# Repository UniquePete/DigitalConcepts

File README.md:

# DigitalConcepts
Digital Concepts LoRa Project<br />
For project details, see http://digitalconcepts.net.au/iot/<br />
<br />
At the moment, I've just dumped a lot of the project files here. I'll get things better
organised and documented in due course.

## Arduino
Most of the material here comprises the sketches and libraries used in the projects described
on the project website identified above. More details to follow.

The one, essentially stand-alone [JavaScript] application/script here is the syntax highlighter.
This script is based on that developed by Indrek Luuk (see https://circuitjournal.com/syntax-highlighter).
The present version is an in-line version that includes some additional Arduino IDE syntax highlighting,
basic HTML syntax highlighting and optional line numbering. It requires the additional definition of
appropriate CSS style definitions (see Highlight.css).

The script and CSS files need to be placed in appropriate directories and referenced in the Head section
of the relevant HTML file:
```
<head>
	<script type="text/javascript" src="scripts/SyntaxHighlighter.js"></script>
	<script>
		// Run any required Syntax Highlighters when the page loads
		document.addEventListener('DOMContentLoaded', processAllArduinoCode);
		document.addEventListener('DOMContentLoaded', processAllHtmlCode);
	</script>
	<link rel="stylesheet" href="styles/Highlight.css">
</head>
```
For the time being, refer to the SyntaxHighlighter page
(https://digitalconcepts.net.au/arduino/index.php?op=SyntaxHighlighter) on the project website for full
details of the capabilities and how to use the script.

## Eagle
These are the Eagle board and schematic files for the PCBs described on the propject website referenced above.
More details to follow.
 
## Fritzing Parts
These are the Fritzing part files, and the related breadboard images to assist in identification, that are
described on the project website referenced above.
More details to follow.

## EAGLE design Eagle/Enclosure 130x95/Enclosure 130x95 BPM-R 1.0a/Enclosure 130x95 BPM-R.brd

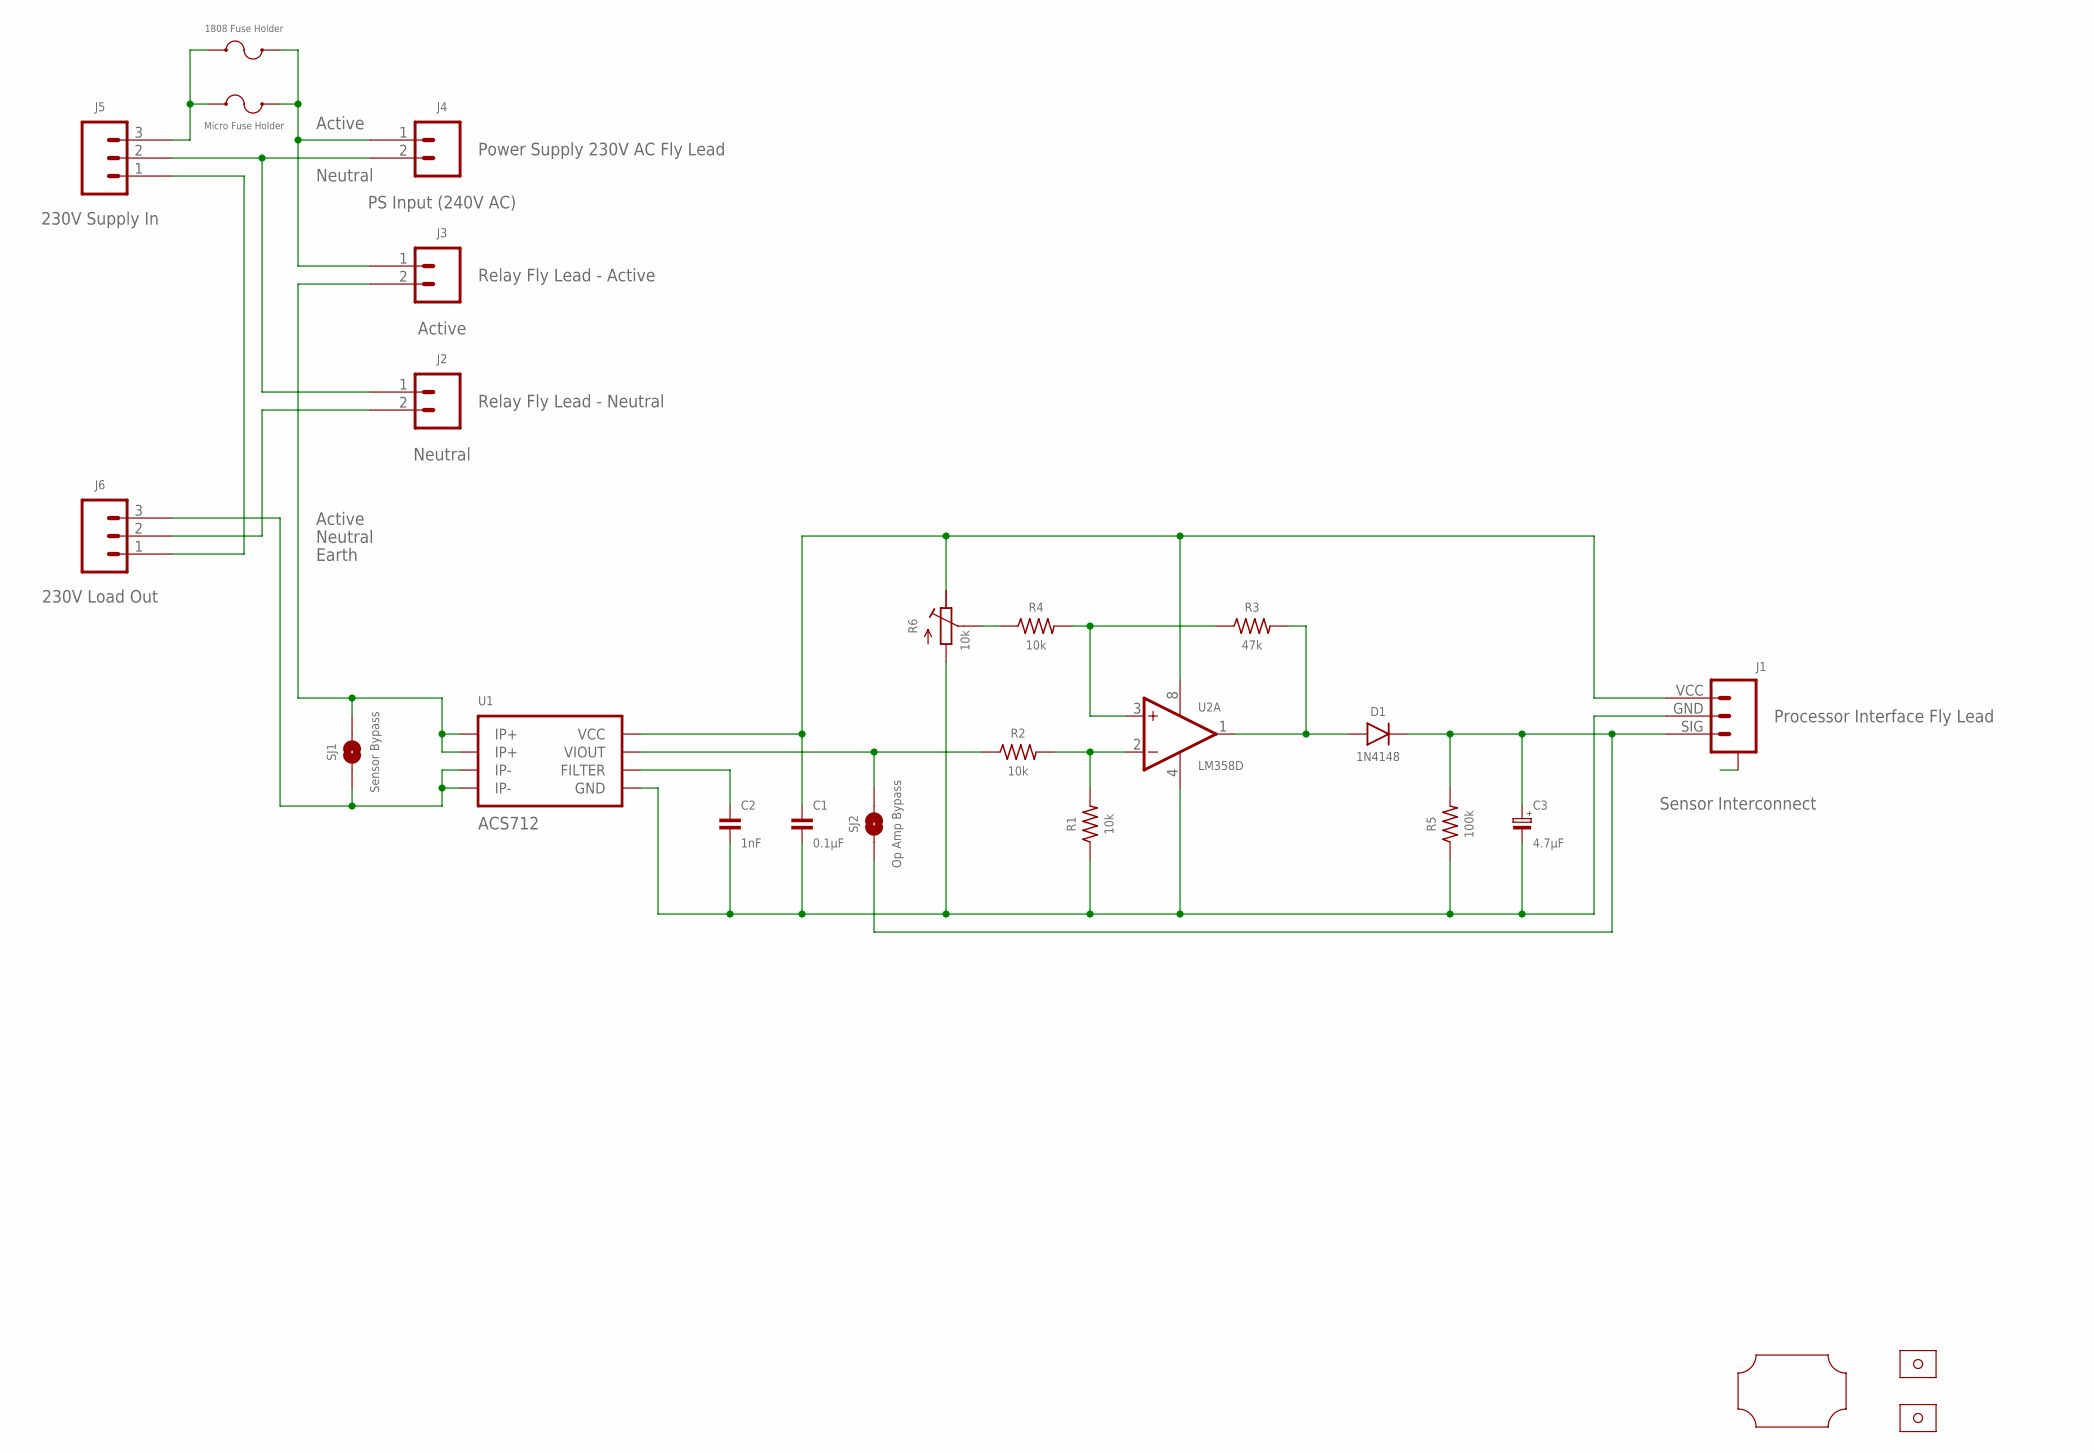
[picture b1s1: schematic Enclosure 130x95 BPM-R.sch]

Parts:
C1: 0.1µF; C0805
C2: 1nF; C0805
C3: 4.7µF; C1206-POLARISED
D1: 1N4148; SOD-323
F2: 1808 Fuse Holder; FUSE-HOLDER-1808
J1: Sensor Interconnect; JST-SH1.0-3-HORIZONTAL-SIG
J2: Neutral; TERMINAL-SCREW-2P
J3: Active; TERMINAL-SCREW-2P
J4: PS Input (240V AC); JST-XH2.4-2-HORIZONTAL
J5: 230V Supply In; TERMINAL-SCREW-3P
J6: 230V Load Out; TERMINAL-SCREW-3P
R1, R2, R4: 10k; R0805
R3: 47k; R0805
R5: 100k; R0805
R6: 10k; RTRIM3386P
SJ1: Sensor Bypass; SJ
SJ2: Op Amp Bypass; SJ
U1: ACS712; SOP-8
U2: LM358D; SOP-8
U$1: PCB-OUTLINE-130X95-MAX-RC-H3; PROTO-130X95-OUTLINE-MAX-RC-H3
U$2: Micro Fuse Holder; FUSE-HOLDER-MICRO
U$4, U$5: STRAIN-RELIEF-SADDLE

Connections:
A: J1.A@1 (A), J1.A@3 (A)
ACTIVE_IN: F2.P$2 (2), J3.1, J4.1, U$2.P$3 (2), U$2.P$4 (2)
ACTIVE_OUT: J3.2, SJ1.2, U1.1 (IP+), U1.2 (IP+)
EARTH: J5.1, J6.1
unnamed: C1.1, J1.VCC (3), R6.1 (E), U1.8 (VCC), U2.8 (V+)
unnamed: C3.1 (+), D1.C (1), J1.SIG (1), R5.2, SJ2.1
unnamed: D1.A (2), R3.2, U2.1 (OUT)
unnamed: R3.1, R4.2, U2.3 (+IN)
unnamed: R4.1, R6.2 (S)
unnamed: F2.P$1 (1), J5.3, U$2.P$1 (1), U$2.P$2 (1)
unnamed: R1.2, R2.2, U2.2 (-IN)
unnamed: J6.3, SJ1.1, U1.3 (IP-), U1.4 (IP-)
unnamed: C1.2, C2.2, C3.2 (-), J1.GND (2), R1.1, R5.1, R6.3 (A), U1.5 (GND), U2.4 (V-)
unnamed: R2.1, SJ2.2, U1.7 (VIOUT)
unnamed: C2.1, U1.6 (FILTER)
NEUTRAL_IN: J2.1, J4.2, J5.2
NEUTRAL_OUT: J2.2, J6.2

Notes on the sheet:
Power Supply 230V AC Fly Lead
Active
Neutral
Relay Fly Lead - Active
Earth
Processor Interface Fly Lead
Relay Fly Lead - Neutral

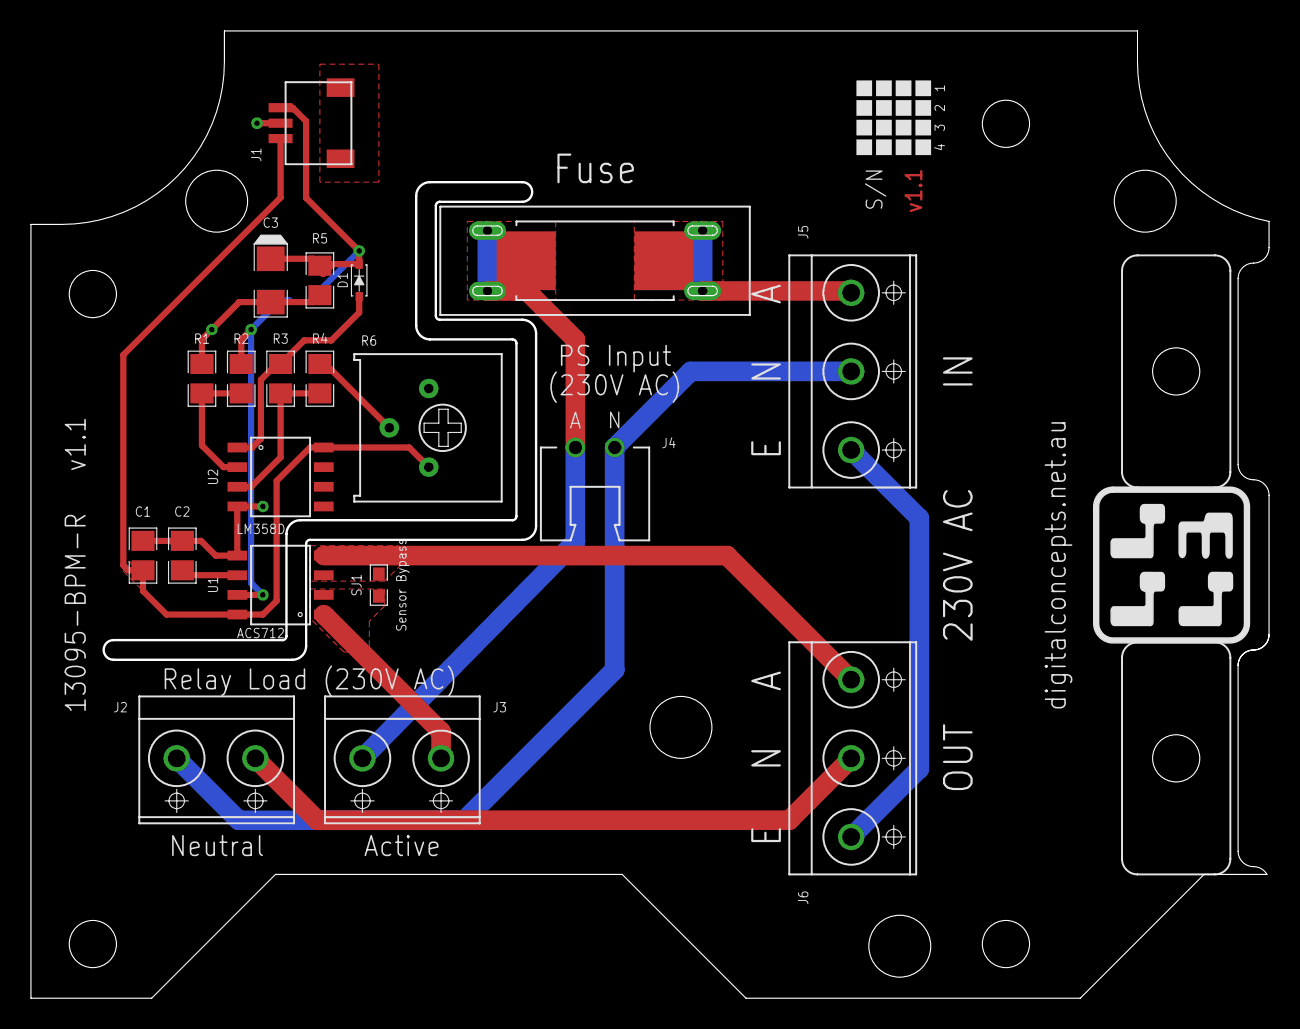
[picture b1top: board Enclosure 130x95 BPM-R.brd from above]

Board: 2 copper layers, 80.0 x 62.5 mm, 25 parts (1 on the bottom side), 17 nets.

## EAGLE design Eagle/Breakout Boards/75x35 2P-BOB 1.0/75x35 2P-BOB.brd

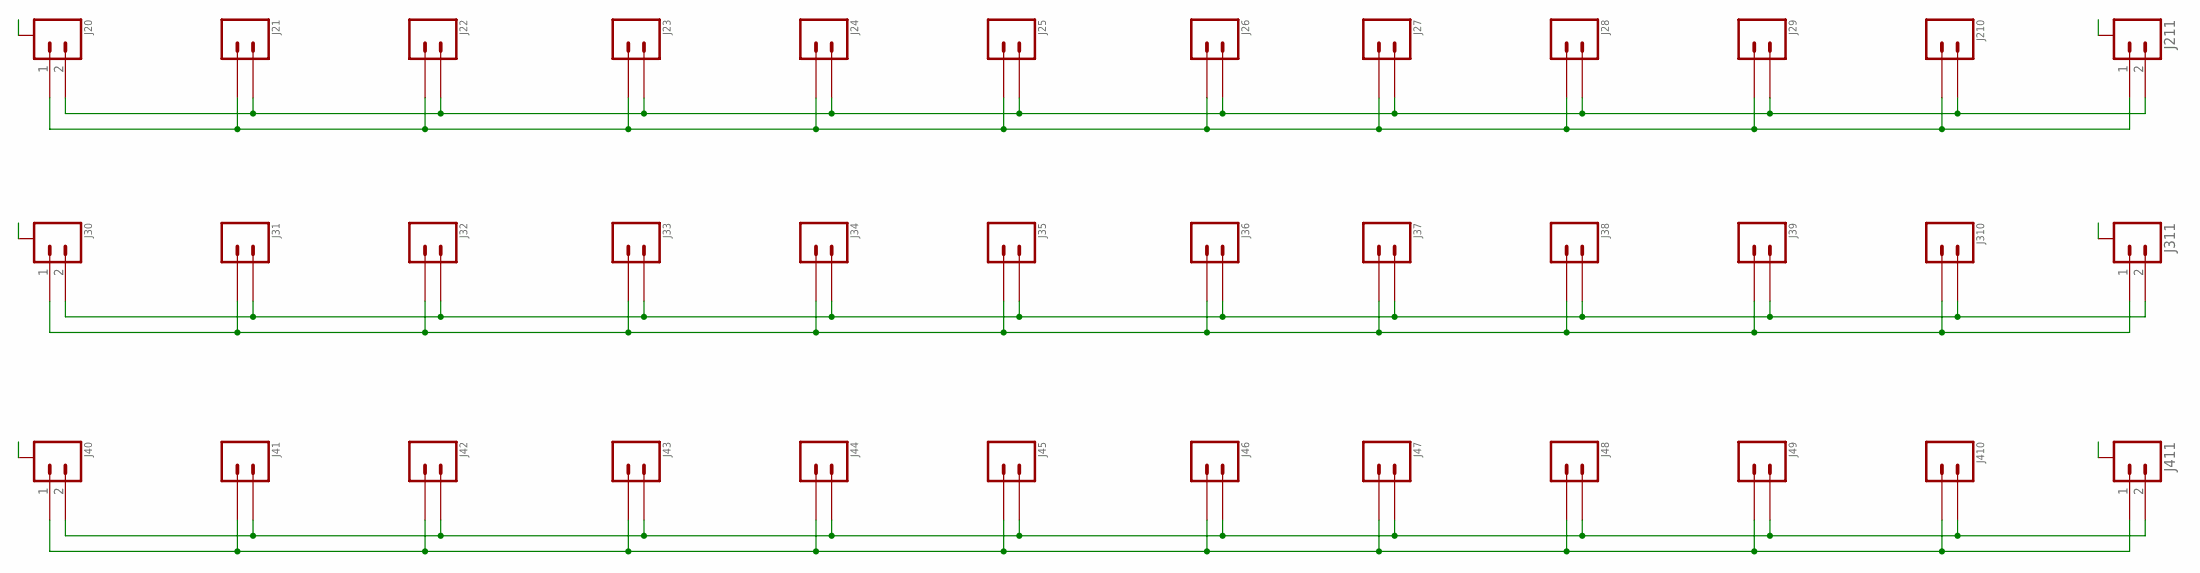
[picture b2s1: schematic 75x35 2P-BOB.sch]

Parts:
J20, J30, J40, J211, J311, J411: JST-SH1.0-2-SMD-VERTICAL; JST-SH1.0-2-VERTICAL
J21, J31, J41, J210, J310, J410: JST-GH1.25-2-VERTICAL
J22, J29, J32, J39, J42, J49: JST-PH2.0-2-VERTICAL
J23, J24, J25, J26, J27, J28, J33, J34, J35, J36, J37, J38, J43, J44, J45, J46, J47, J48: HEADER-1X2-GENERIC; CONN_02-GENERIC

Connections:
A: J20.A@1 (A), J20.A@2 (A), J30.A@1 (A), J30.A@2 (A), J40.A@1 (A), J40.A@2 (A), J211.A@1 (A), J211.A@2 (A), J311.A@1 (A), J311.A@2 (A), J411.A@1 (A), J411.A@2 (A)
unnamed: J20.1, J21.1, J22.1, J23.1, J24.1, J25.1, J26.1, J27.1, J28.1, J29.1, J210.1, J211.1
unnamed: J30.2, J31.2, J32.2, J33.2, J34.2, J35.2, J36.2, J37.2, J38.2, J39.2, J310.2, J311.2
unnamed: J30.1, J31.1, J32.1, J33.1, J34.1, J35.1, J36.1, J37.1, J38.1, J39.1, J310.1, J311.1
unnamed: J40.2, J41.2, J42.2, J43.2, J44.2, J45.2, J46.2, J47.2, J48.2, J49.2, J410.2, J411.2
unnamed: J40.1, J41.1, J42.1, J43.1, J44.1, J45.1, J46.1, J47.1, J48.1, J49.1, J410.1, J411.1
unnamed: J20.2, J21.2, J22.2, J23.2, J24.2, J25.2, J26.2, J27.2, J28.2, J29.2, J210.2, J211.2

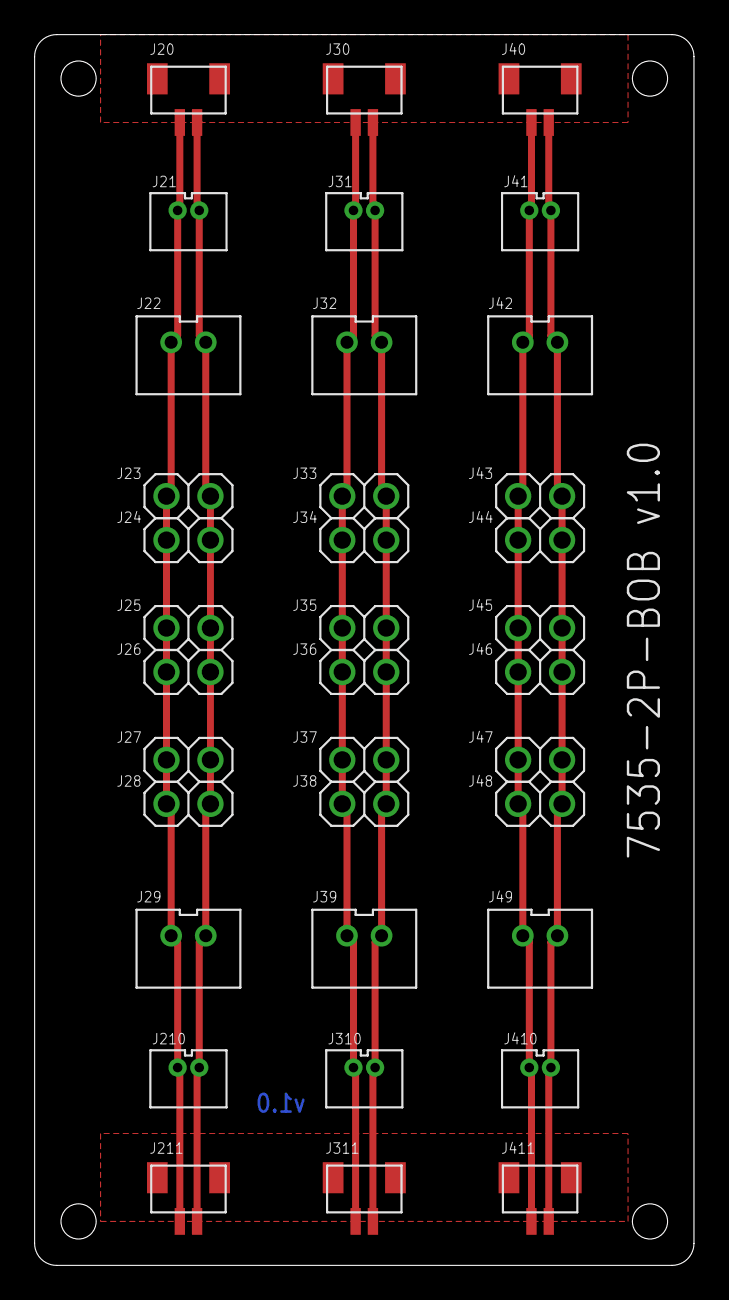
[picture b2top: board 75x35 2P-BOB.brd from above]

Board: 2 copper layers, 38.1 x 71.1 mm, 36 parts (0 on the bottom side), 7 nets.

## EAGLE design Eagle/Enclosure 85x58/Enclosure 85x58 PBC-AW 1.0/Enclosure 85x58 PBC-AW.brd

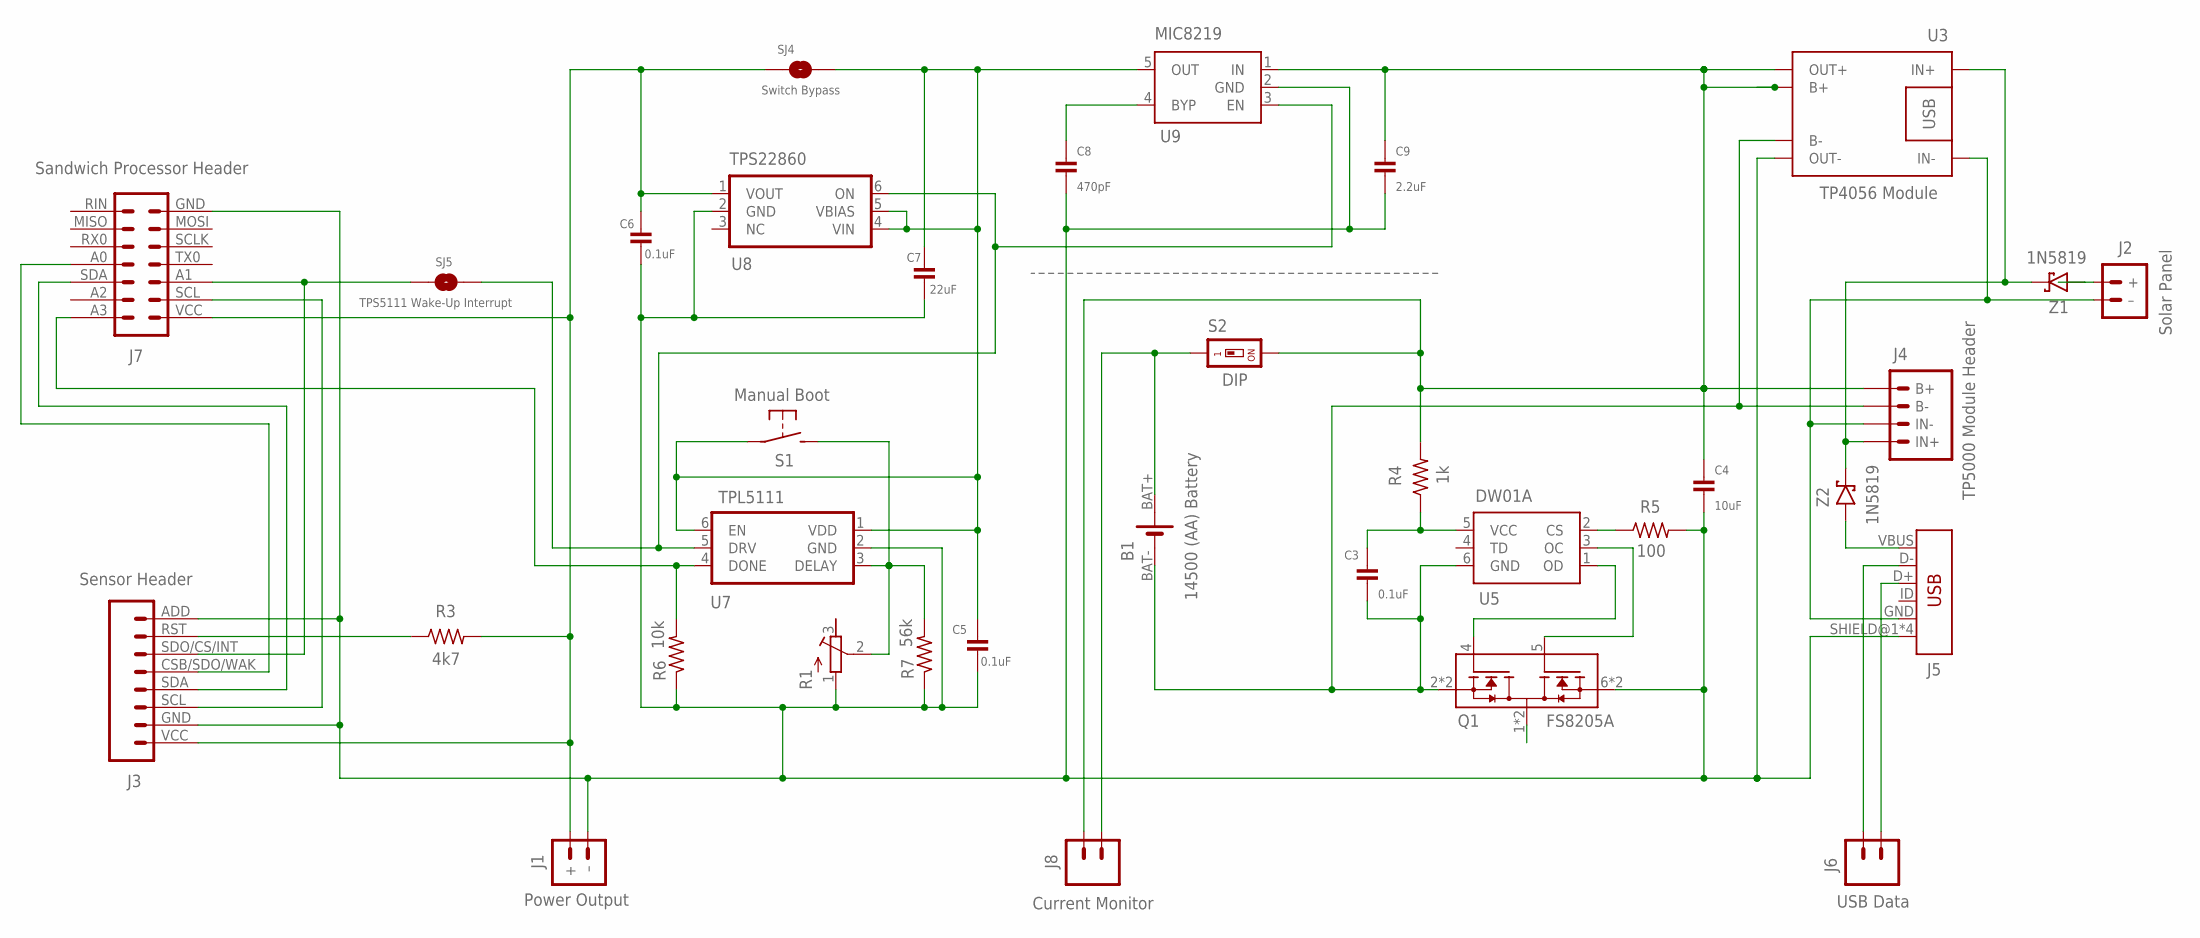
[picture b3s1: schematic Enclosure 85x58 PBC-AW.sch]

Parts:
B1: 14500 (AA) Battery; BATTERY-14500
C3, C5, C6: 0.1uF; C0805
C4: 10uF; C0805
C7: 22uF; C0805
C8: 470pF; C0805
C9: 2.2uF; C0805
J1: Power Output; JST-PH1.25
J2: Solar Panel; JST-PH2.0
J3: Sensor Header; CONN_08-SENSOR
J4: TP5000 Module Header; CONN_04-GENERIC
J5: USB; USB-MINIB
J6: USB Data; CONN_02-GENERIC
J7: Sandwich Processor Header; CONN_2X7-WIJNAND-PROCESSOR
J8: JST-PH2.0-MALE-HORIZONTALJST-PTH-2; JST-2-PTH
Q1: FS8205A; SOP65P640X120-8N
R1: RESISTOR-TRIMM64W; RTRIM64W
R3: 4k7; R0805
R4: 1k; R0805
R5: 100; R0805
R6: 10k; R0805
R7: 56k; R0805
S1: Manual Boot; SWITCH-2-PAD
S2: DIP; SMS-001
SJ4: Switch Bypass; SJ
SJ5: TPS5111 Wake-Up Interrupt; SJ
U3: TP4056 Module; BATTERY-CHARGER-LI-PROT
U5: DW01A; SOT23-6
U7: TPL5111; SOT-23-6
U8: TPS22860; SOT-23-6
U9: MIC8219; SOT-23-5
Z1, Z2: 1N5819; SOD-123

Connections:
GND: C4.2, C5.2, C6.2, C7.2, C8.2, C9.2, J1.- (–), J3.ADD (8), J3.GND (2), J5.SHIELD@1 (SHIELD), J5.SHIELD@2 (SHIELD), J5.SHIELD@3 (SHIELD), J5.SHIELD@4 (SHIELD), J7.GND (7), Q1.6 (S2), Q1.7 (S2), R1.1 (A), R5.2, R6.1, R7.1, U3.OUT-, U7.2 (GND), U8.2 (GND), U9.2 (GND)
unnamed: J2.+, Z1.A
unnamed: J2.- (–), J4.2 (IN-), J5.GND, U3.IN-
unnamed: R5.1, U5.2 (CS)
unnamed: Q1.1 (D12), Q1.8 (D12)
unnamed: J4.1 (IN+), U3.IN+, Z1.C, Z2.C
unnamed: C4.1, C9.1, J4.4 (B+), J8.1, R4.2, S2.2, U3.B+, U3.OUT+, U9.1 (IN)
unnamed: C8.1, U9.4 (BYP)
unnamed: J3.SCL (3), J7.SCL (2)
unnamed: J3.RST (7), R3.1
unnamed: J3.CSB/SDO/WAK (5), J7.A0 (11)
unnamed: J3.SDA (4), J7.SDA (12)
unnamed: B1.BAT+, J8.2, S2.1
unnamed: Q1.5 (G2), U5.3 (OC)
unnamed: J5.VBUS, Z2.A
unnamed: Q1.4 (G1), U5.1 (OD)
unnamed: J5.D+, J6.2
unnamed: C3.1, R4.1, U5.5 (VCC)
unnamed: B1.BAT-, C3.2, J4.3 (B-), Q1.2 (S1), Q1.3 (S1), U3.B-, U5.6 (GND)
unnamed: J5.D-, J6.1
unnamed: R1.2 (S), R7.2, S1.P$2 (S), U7.3 (DELAY)
unnamed: C5.1, C7.1, S1.P$1, SJ4.2, U7.1 (VDD), U7.6 (EN), U8.4 (VIN), U8.5 (VBIAS), U9.5 (OUT)
unnamed: SJ5.2, U7.5 (DRV), U8.6 (ON), U9.3 (EN)
unnamed: J7.A3 (14), R6.2, U7.4 (DONE)
unnamed: J3.SDO/CS/INT (6), J7.A1 (3), SJ5.1
VCC: C6.1, J1.+, J3.VCC (1), J7.VCC (1), R3.2, SJ4.1, U8.1 (VOUT)

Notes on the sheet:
Current Monitor

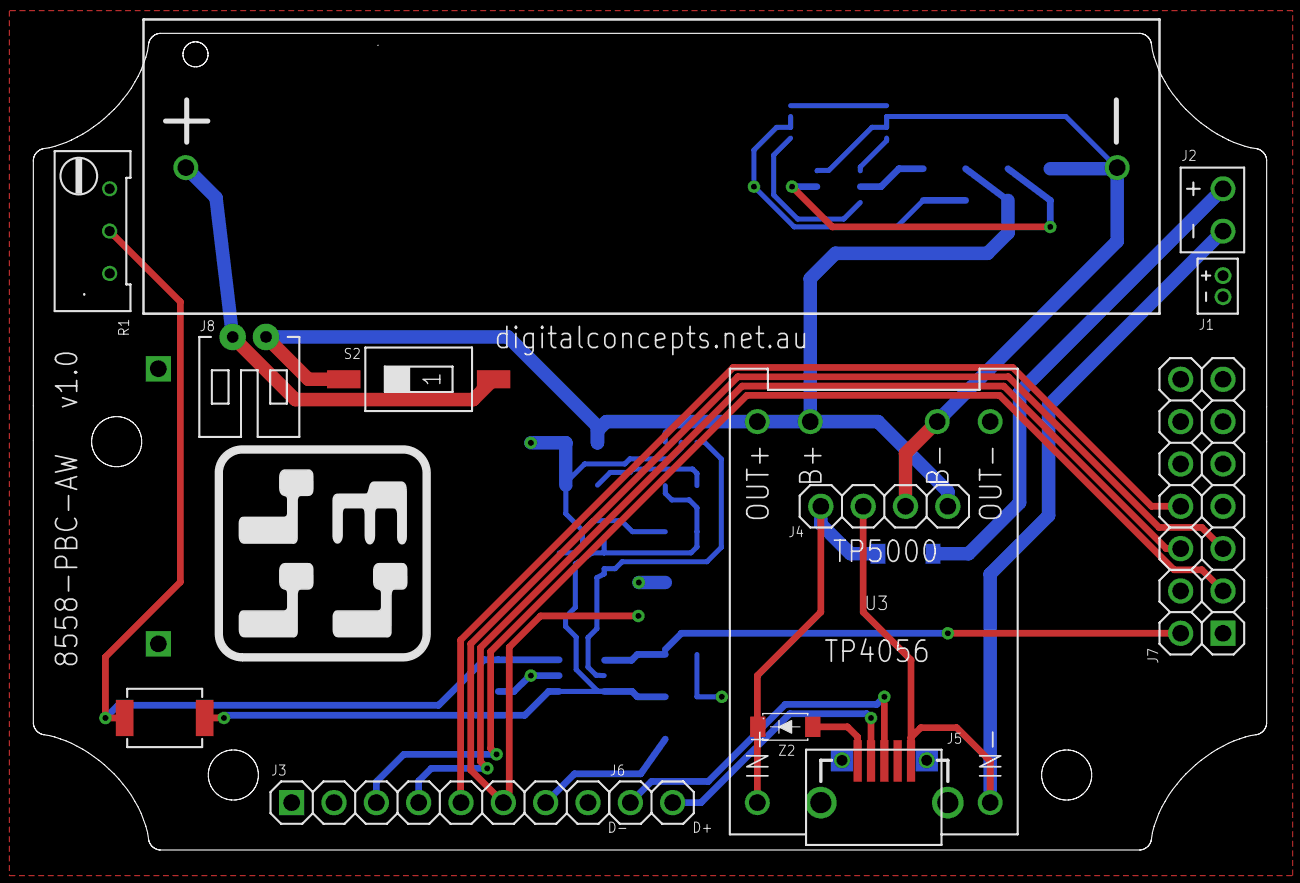
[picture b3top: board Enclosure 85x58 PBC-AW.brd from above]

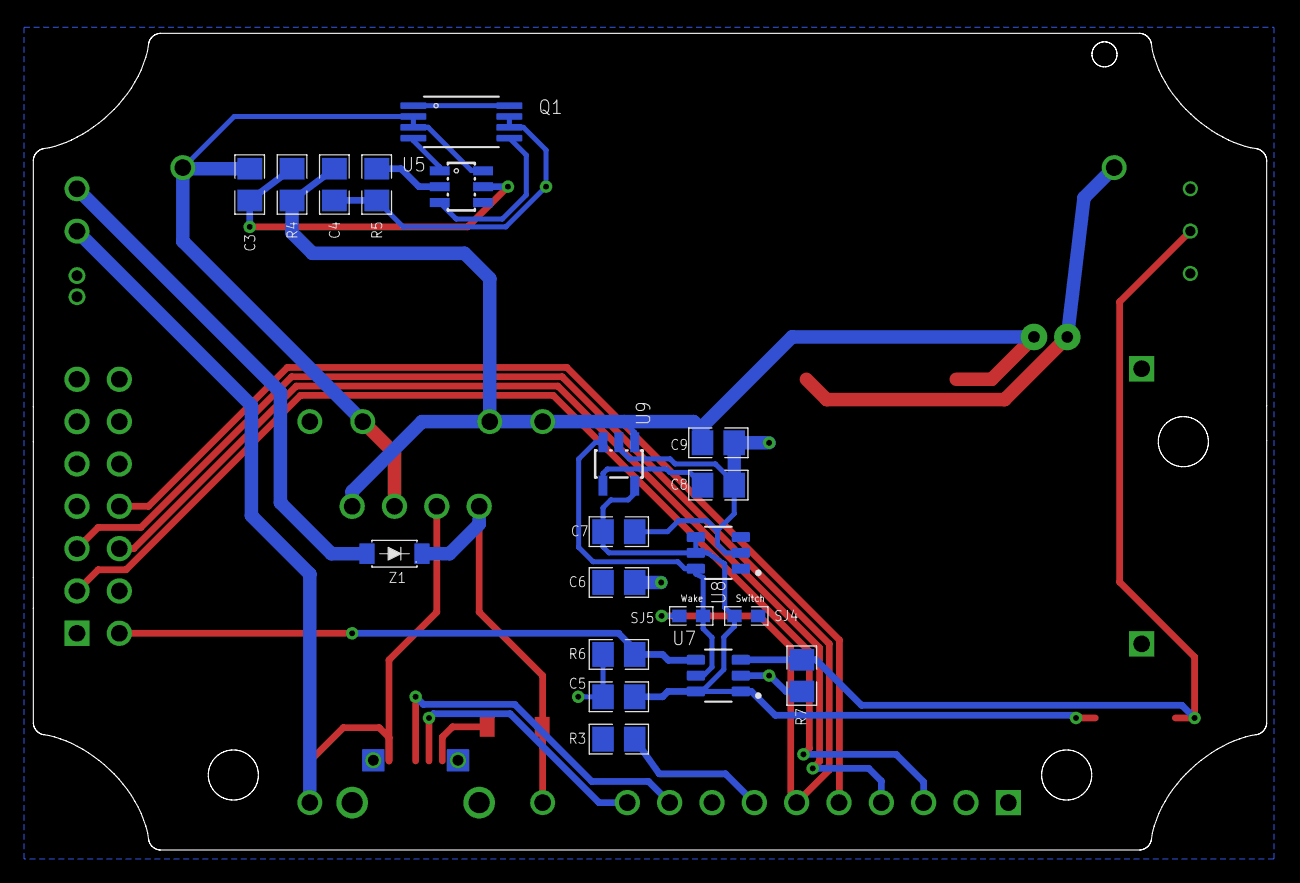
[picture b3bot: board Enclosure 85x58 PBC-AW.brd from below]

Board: 2 copper layers, 74.0 x 49.0 mm, 34 parts (20 on the bottom side), 26 nets.

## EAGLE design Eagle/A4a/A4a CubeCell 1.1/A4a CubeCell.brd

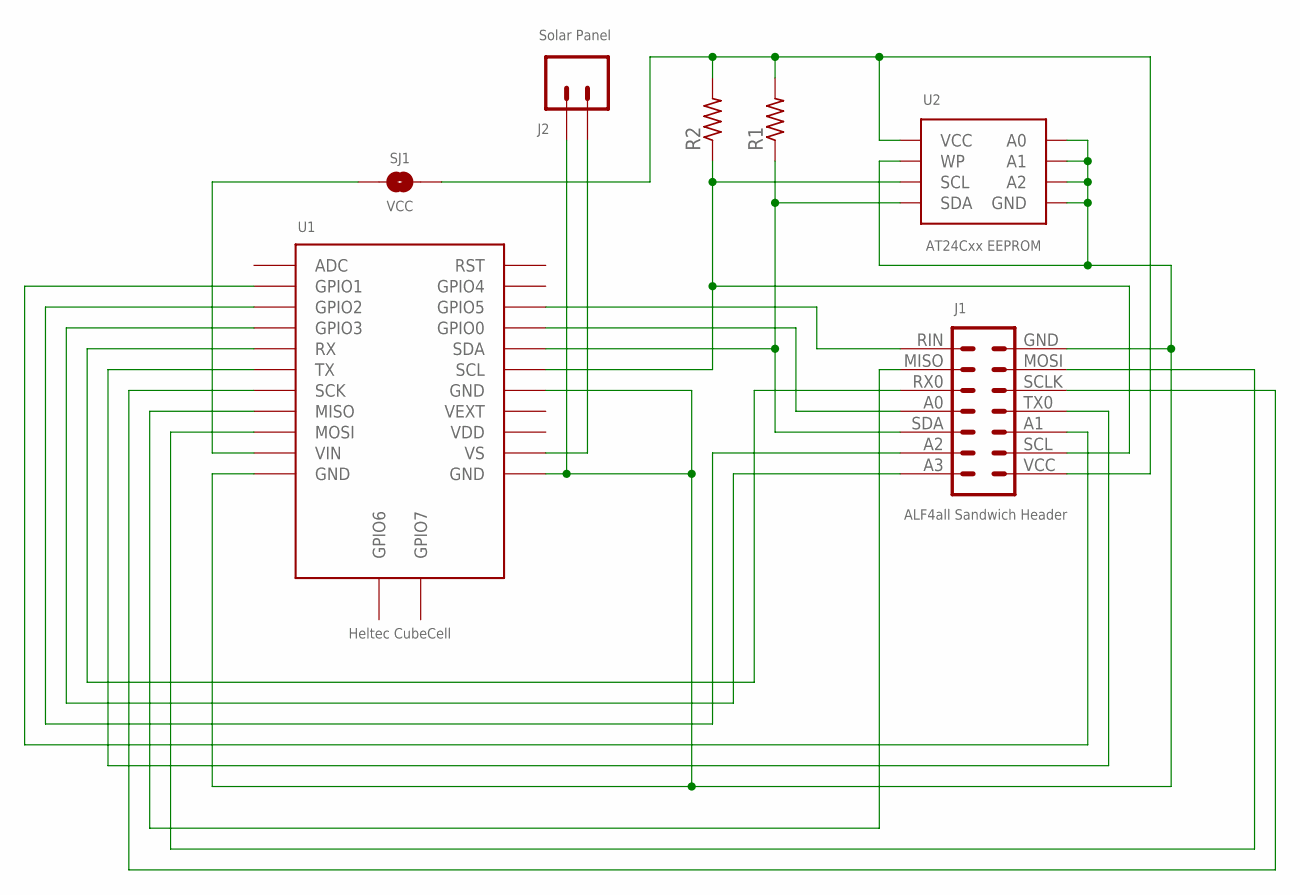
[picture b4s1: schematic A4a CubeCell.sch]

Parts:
J1: ALF4all Sandwich Header; CONN_2X7-ALF4ALL-PROCESSOR-B
J2: Solar Panel; JST-PH2.0-2-HORIZONTAL
R1, R2: RESISTORR0805; R0805
SJ1: VCC; SJ
U1: Heltec CubeCell; HELTEC-CUBECELL
U2: AT24Cxx EEPROM; SOP-8-WITH-VIAS-4-5

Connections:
GND: J1.GND (7), J2.- (1), U1.GND@11 (GND), U1.GND@14 (GND), U1.GND@18 (GND), U2.P$1 (A0), U2.P$2 (A1), U2.P$3 (A2), U2.P$4 (GND), U2.P$4@VIA (GND), U2.P$7 (WP)
unnamed: J1.SCL (2), R2.1, U1.SCL, U2.P$6 (SCL)
unnamed: J1.SDA (12), R1.1, U1.SDA, U2.P$5 (SDA), U2.P$5@VIA (SDA)
unnamed: J1.A2 (13), U1.GPIO2
unnamed: J1.A3 (14), U1.GPIO3
unnamed: J1.A1 (3), U1.GPIO1
unnamed: J1.A0 (11), U1.GPIO0
unnamed: J1.TX0 (4), U1.TX
unnamed: J1.RX0 (10), U1.RX
unnamed: J1.SCLK (5), U1.SCK
unnamed: J1.MISO (9), U1.MISO
unnamed: J1.MOSI (6), U1.MOSI
unnamed: J1.RIN (8), U1.GPIO5
unnamed: J2.+ (2), U1.VS
unnamed: SJ1.1, U1.VIN
VCC: J1.VCC (1), R1.2, R2.2, SJ1.2, U2.P$8 (VCC)

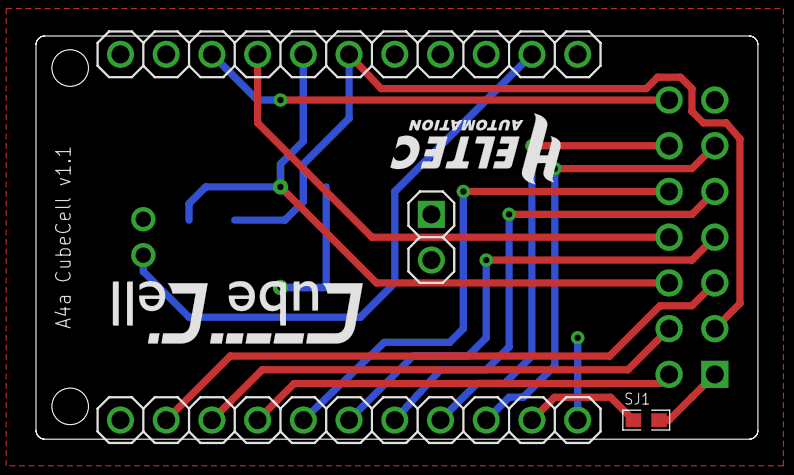
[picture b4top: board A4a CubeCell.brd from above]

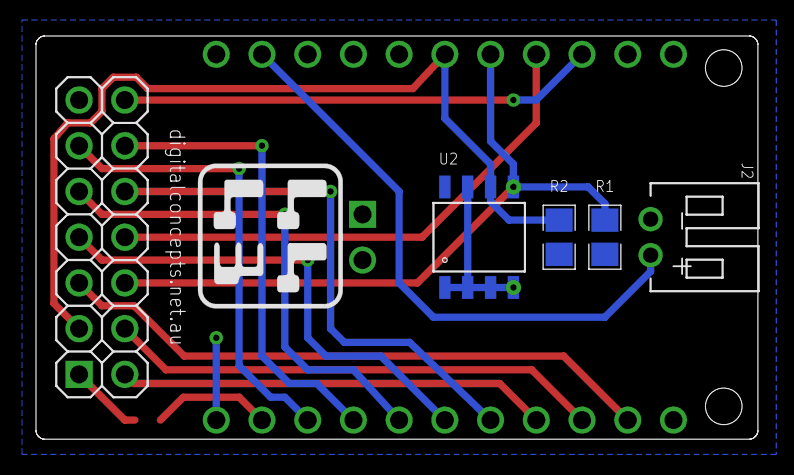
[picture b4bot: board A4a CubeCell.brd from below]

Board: 2 copper layers, 40.1 x 22.4 mm, 7 parts (4 on the bottom side), 16 nets.

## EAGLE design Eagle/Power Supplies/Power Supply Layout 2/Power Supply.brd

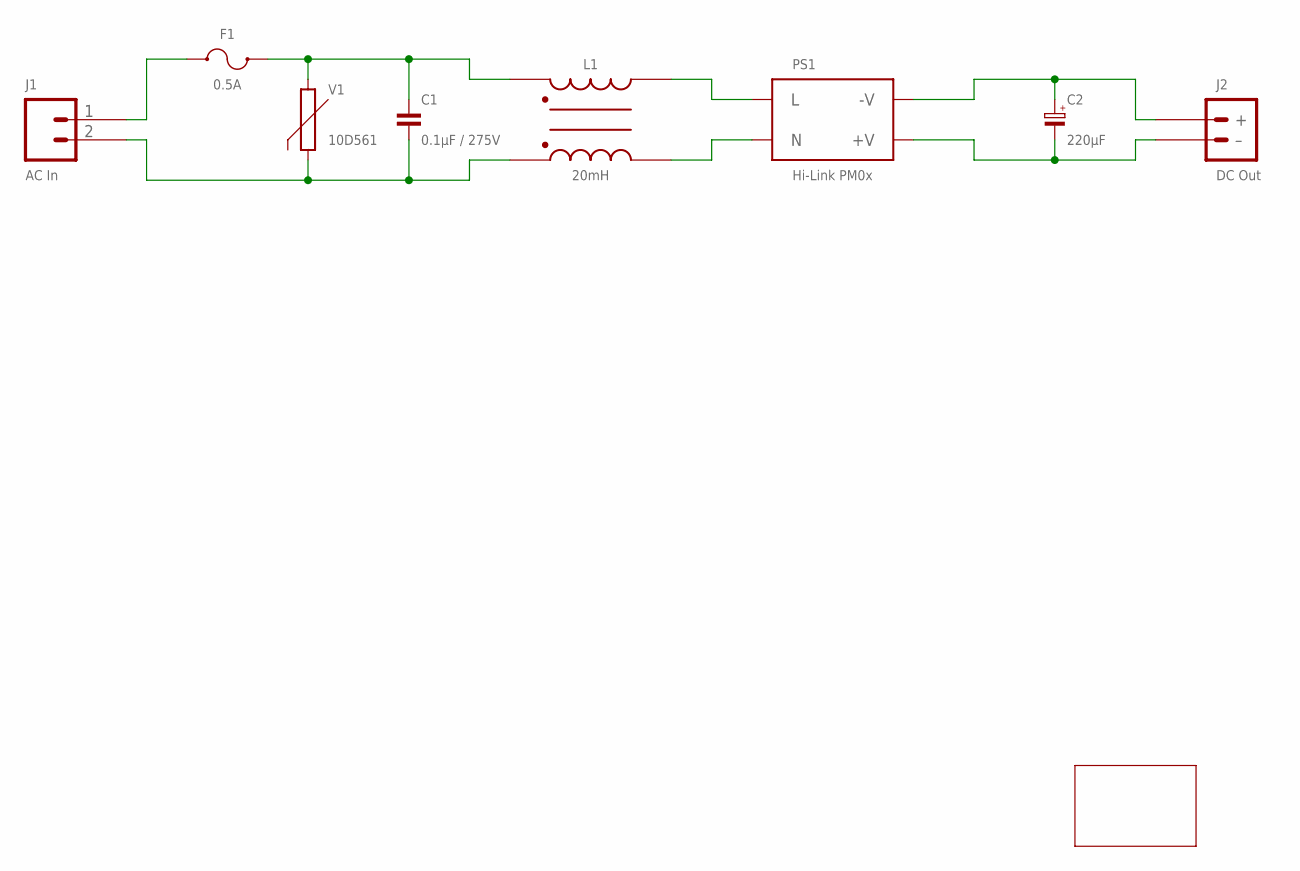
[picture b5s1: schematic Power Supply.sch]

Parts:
C1: 0.1µF / 275V; CAPACITOR-TENTA-SUPPRESSION
C2: 220µF; E5-10,5
F1: 0.5A; FUSE-HOLDER-1808
J1: AC In; JST-XH2.4-2-HORIZONTAL
J2: DC Out; JST-PH2.0-2-VERTICAL-POWER
L1: 20mH; INDUCTOR-UU9.8
PCB1: PCB-OUTLINE-64X31; PCB-POWER-SUPPLY
PS1: Hi-Link PM0x; HI-LINK
V1: 10D561; VARISTOR-10D561

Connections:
unnamed: F1.P$1 (1), J1.1
unnamed: C1.P$1 (1), F1.P$2 (2), L1.P$1 (1), V1.2
unnamed: L1.P$2 (2), PS1.AC-L (L)
unnamed: C1.P$2 (2), J1.2, L1.P$4 (4), V1.1
unnamed: L1.P$3 (3), PS1.AC-N (N)
unnamed: C2.+, J2.+, PS1.-VO (-V)
unnamed: C2.-, J2.- (–), PS1.+VO (+V)

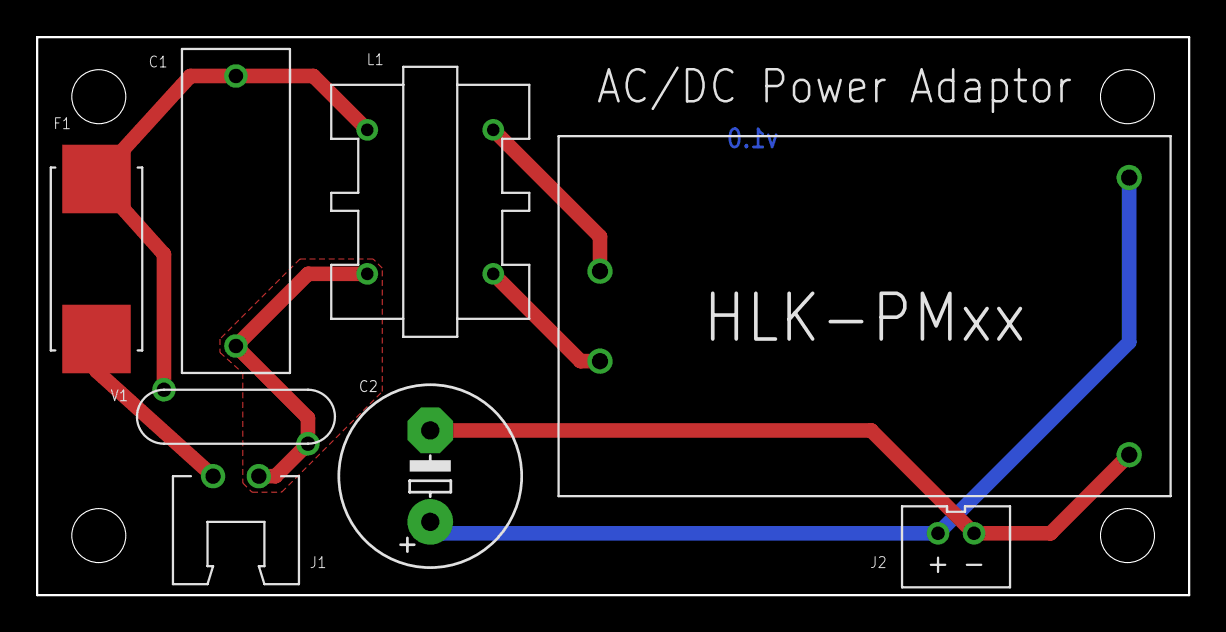
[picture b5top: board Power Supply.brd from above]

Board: 2 copper layers, 64.0 x 31.0 mm, 9 parts (0 on the bottom side), 7 nets.

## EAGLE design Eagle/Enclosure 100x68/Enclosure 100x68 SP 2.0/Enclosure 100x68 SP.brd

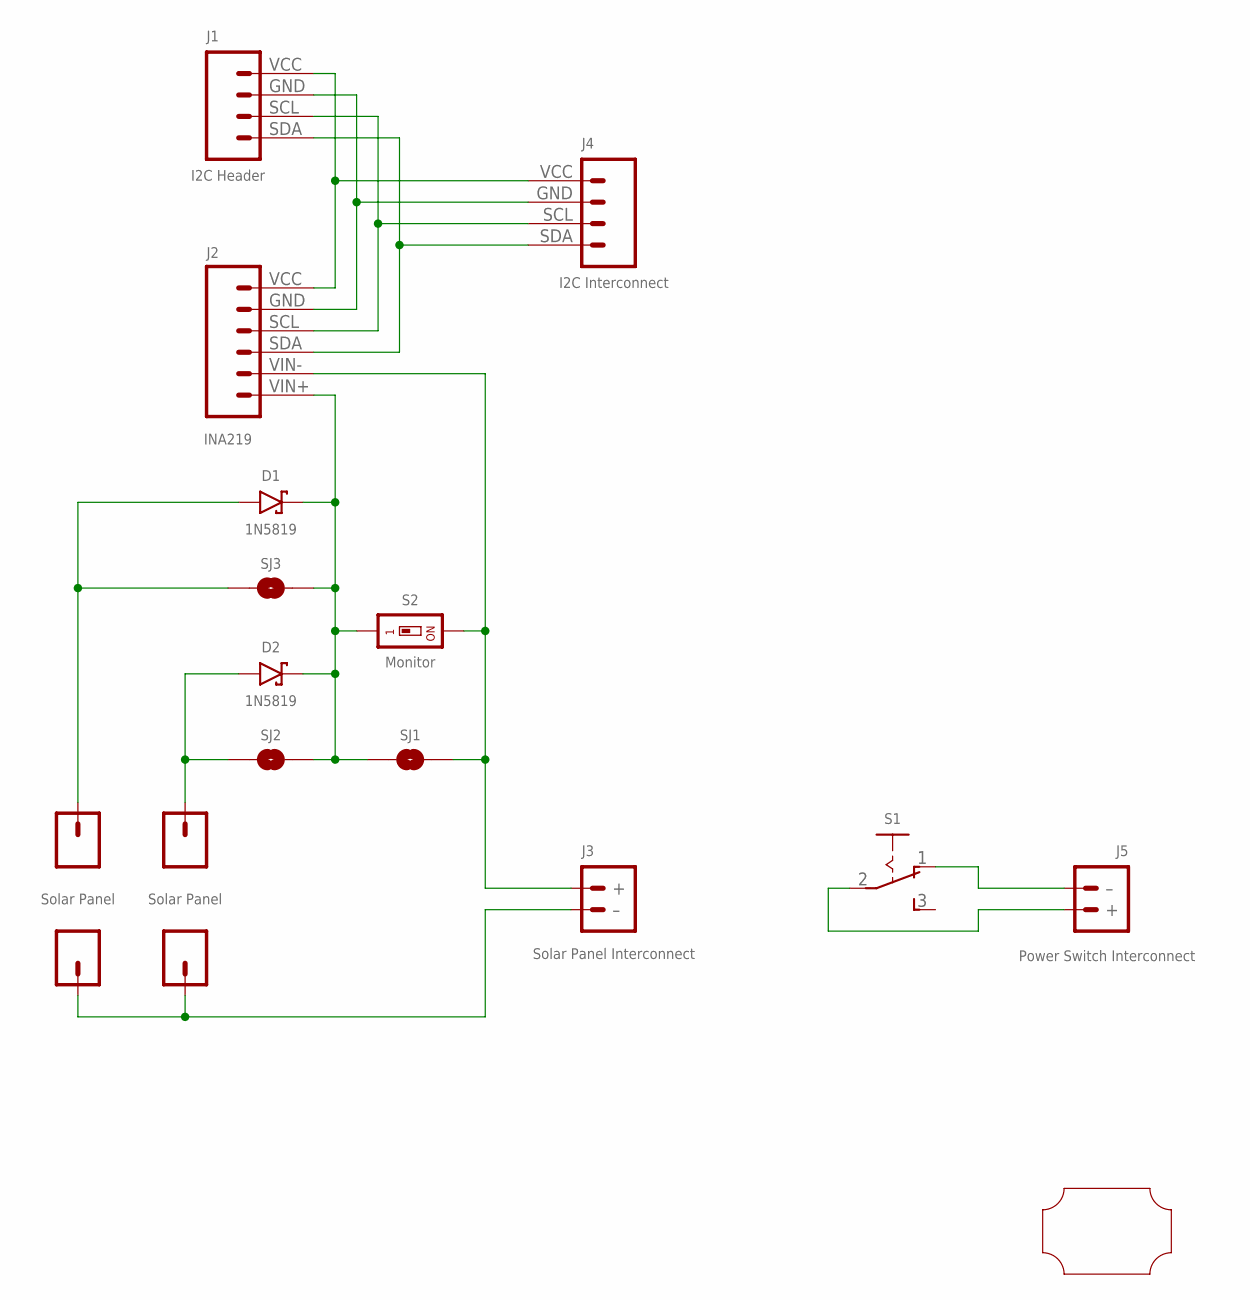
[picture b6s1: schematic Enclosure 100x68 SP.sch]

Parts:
+, +1: Solar Panel; PAD-SMD-GENERIC
-, -1: Solar Panel; PAD-SMD-GENERIC
D1, D2: 1N5819; SOD-123
J1: I2C Header; CONN_04-I2C
J2: INA219; CONN_06-INA219
J3: Solar Panel Interconnect; JST-PH2.0-2-HORIZONTAL
J4: I2C Interconnect; JST-PH2.0-4-HORIZONTAL
J5: Power Switch Interconnect; JST-PH2.0-2-HORIZONTAL
S1: SWITCH-SLIDE-SPDT; SWITCH-SPDT-PTH
S2: Monitor; SMD-001
SJ1, SJ2, SJ3: SJ
U$1: PROTO-34X22-SP

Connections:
GND: J1.GND (2), J2.GND (2), J4.GND (3)
unnamed: J1.SDA (4), J2.SDA (4), J4.SDA (1)
unnamed: J1.SCL (3), J2.SCL (3), J4.SCL (2)
unnamed: +1.P$1, D1.A, SJ3.1
unnamed: J2.VIN- (5), J3.1 (+), S2.2, SJ1.2
unnamed: D1.C, D2.C, J2.VIN+ (6), S2.1, SJ1.1, SJ2.2, SJ3.2
unnamed: J5.1 (+), S1.2
unnamed: -.P$1, -1.P$1, J3.2 (–)
unnamed: +.P$1, D2.A, SJ2.1
unnamed: J5.2 (–), S1.1 (O)
VCC: J1.VCC (1), J2.VCC (1), J4.VCC (4)
